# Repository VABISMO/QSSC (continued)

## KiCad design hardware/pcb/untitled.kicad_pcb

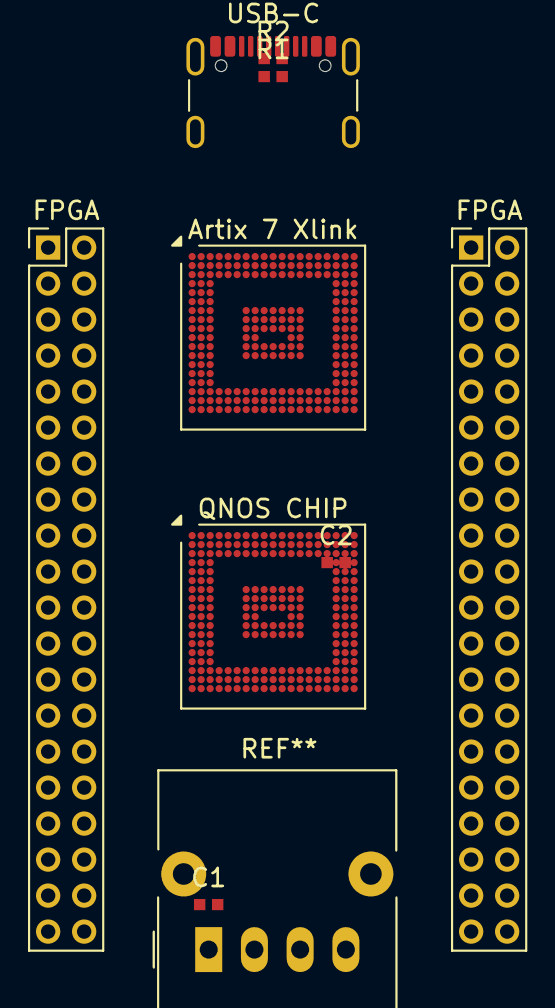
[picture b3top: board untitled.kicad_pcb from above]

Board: 2 copper layers, 9 parts (0 on the bottom side), 7 nets, no tracks yet.

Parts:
Artix 7 Xlink: Xilinx_CPG236
C1, C2: 0.1uF; C_0402_1005Metric
FPGA: PinHeader_2x20_P2.00mm_Vertical
FPGA#2: PinHeader_2x20_P2.00mm_Vertical
QNOS CHIP: QNOS CHIP; Xilinx_CPG236
R1, R2: 22; R_0402_1005Metric
USB-C: USB_C_Receptacle_GCT_USB4105-xx-A_16P_TopMnt_Hori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; USB_C_Receptacle_GCT_USB4105-xx-A_16P_TopMnt_Horizontal

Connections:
Fiber_Out: Artix 7 Xlink.D18, Artix 7 Xlink.U17, QNOS CHIP.D18, QNOS CHIP.U17
GND: Artix 7 Xlink.A1, Artix 7 Xlink.A3, Artix 7 Xlink.A5, Artix 7 Xlink.A7, Artix 7 Xlink.A9, Artix 7 Xlink.A19, Artix 7 Xlink.B3, Artix 7 Xlink.B5, Artix 7 Xlink.B7, Artix 7 Xlink.B8, Artix 7 Xlink.B9, Artix 7 Xlink.B14, Artix 7 Xlink.C2, Artix 7 Xlink.C3, Artix 7 Xlink.C4, Artix 7 Xlink.C6, Artix 7 Xlink.C10, Artix 7 Xlink.D3, Artix 7 Xlink.E3, Artix 7 Xlink.F1, Artix 7 Xlink.F2, Artix 7 Xlink.F19, Artix 7 Xlink.G1, Artix 7 Xlink.G8, Artix 7 Xlink.G11, Artix 7 Xlink.G19, Artix 7 Xlink.H7, Artix 7 Xlink.H8, Artix 7 Xlink.H11, Artix 7 Xlink.H12, Artix 7 Xlink.J11, Artix 7 Xlink.J12, Artix 7 Xlink.K12, Artix 7 Xlink.L8, Artix 7 Xlink.L11, Artix 7 Xlink.M9, Artix 7 Xlink.M11, Artix 7 Xlink.M13, Artix 7 Xlink.N9, Artix 7 Xlink.N12, Artix 7 Xlink.N13, Artix 7 Xlink.P2, Artix 7 Xlink.T19, Artix 7 Xlink.U6, Artix 7 Xlink.V1, Artix 7 Xlink.V6, Artix 7 Xlink.V18, Artix 7 Xlink.W1, Artix 7 Xlink.W12, Artix 7 Xlink.W17, C1.2, C2.2, QNOS CHIP.A1, QNOS CHIP.A3, QNOS CHIP.A5, QNOS CHIP.A7, QNOS CHIP.A9, QNOS CHIP.A19, QNOS CHIP.B3, QNOS CHIP.B5, QNOS CHIP.B7, QNOS CHIP.B9, QNOS CHIP.B14, QNOS CHIP.C2, QNOS CHIP.C3, QNOS CHIP.C4, QNOS CHIP.C6, QNOS CHIP.C10, QNOS CHIP.C19, QNOS CHIP.D3, QNOS CHIP.E3, QNOS CHIP.F1, QNOS CHIP.F2, QNOS CHIP.F19, QNOS CHIP.G1, QNOS CHIP.G8, QNOS CHIP.G11, QNOS CHIP.G19, QNOS CHIP.H7, QNOS CHIP.H8, QNOS CHIP.H11, QNOS CHIP.H12, QNOS CHIP.J11, QNOS CHIP.J12, QNOS CHIP.K12, QNOS CHIP.L8, QNOS CHIP.L11, QNOS CHIP.M9, QNOS CHIP.M11, QNOS CHIP.M13, QNOS CHIP.N9, QNOS CHIP.N12, QNOS CHIP.N13, QNOS CHIP.P2, QNOS CHIP.U6, QNOS CHIP.V1, QNOS CHIP.V6, QNOS CHIP.V18, QNOS CHIP.W1, QNOS CHIP.W12, QNOS CHIP.W17, USB-C.A1, USB-C.A5, USB-C.A12, USB-C.B1, USB-C.B5, USB-C.B12, USB-C.S1
USB_D+: Artix 7 Xlink.E19, R1.1, USB-C.A6, USB-C.B6
USB_D-: Artix 7 Xlink.E18, Artix 7 Xlink.F18, R2.1, USB-C.A7, USB-C.B7
Vcc: Artix 7 Xlink.C14, Artix 7 Xlink.C18, Artix 7 Xlink.F17, Artix 7 Xlink.M17, Artix 7 Xlink.R17, Artix 7 Xlink.U13, C1.1, C2.1, QNOS CHIP.F17, USB-C.A4, USB-C.A9, USB-C.B4, USB-C.B9
chip_D+: QNOS CHIP.E19, R1.2
chip_D-: QNOS CHIP.F18, R2.2

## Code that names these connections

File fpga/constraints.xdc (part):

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# Pin assignments are derived from the datasheet-correct CSG324 ball map
# (.tmpwork/fpga_csg324_map.json, parsed from the real KiCad Artix-7 symbol
# and verified against UG475 / DS181). All six VCCO banks are powered at
# 3.3 V (LVCMOS33). clk_100mhz is on a clock-capable (MRCC) pin.
#
# Parallel architecture: 64 emitters driven by 3x TLC5947 constant-current
# LED drivers over a 4-wire SPI (em_sclk/sin/xlat/blank), and 64 photo-
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# clk_100mhz -> B8, the P-side of an MRCC pair (IO_L..P.._MRCC_):
# per UG472 the single-ended clock INPUT takes the dedicated, delay-
# compensated route to the MMCM (no CLOCK_DEDICATED_ROUTE FALSE needed).
set_property PACKAGE_PIN B8   [get_ports clk_100mhz]
set_property IOSTANDARD LVCMOS33 [get_ports clk_100mhz]
create_clock -name sys_clk -period 10.000 [get_ports clk_100mhz]

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# (chip0 only -- push-pull, all 4 finish a simultaneous CONVST together),
# adc_cs[3:0] (per-chip select), adc_resetn (shared reset, active-low). The
# +/-5V range is HW-pin-strapped on each AD7616 (no MOSI / config writes).
set_property PACKAGE_PIN A18  [get_ports adc_convst]
set_property PACKAGE_PIN B18  [get_ports adc_sclk]
set_property PACKAGE_PIN D18  [get_ports adc_miso]
set_property PACKAGE_PIN E18  [get_ports adc_busy]
set_property PACKAGE_PIN M18  [get_ports adc_resetn]
set_property PACKAGE_PIN F18  [get_ports {adc_cs[0]}]
set_property PACKAGE_PIN G18  [get_ports {adc_cs[1]}]
set_property PACKAGE_PIN J18  [get_ports {adc_cs[2]}]
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# em_blank (global blank/PWM gate). 3x TLC5947 daisy-chain SIN->SOUT for 72
# channels (64 used); each emitter cathode is a TLC5947 OUTn, anode = +5V.
# 12-bit PWM grayscale per channel -> parallel multi-emitter drive.
set_property PACKAGE_PIN V1   [get_ports em_sclk]
set_property PACKAGE_PIN V2   [get_ports em_sin]
set_property PACKAGE_PIN V4   [get_ports em_xlat]
set_property PACKAGE_PIN V5   [get_ports em_blank]
set_property IOSTANDARD LVCMOS33 [get_ports em_sclk]
set_property IOSTANDARD LVCMOS33 [get_ports em_sin]
set_property IOSTANDARD LVCMOS33 [get_ports em_xlat]
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
# ---- MW RF-switch gate pulse (APPLY_PULSE duration) ------------------------
# Gates the external RF switch between the ADF4351 output and the antenna.
set_property PACKAGE_PIN L1   [get_ports mw_gate]
set_property IOSTANDARD LVCMOS33 [get_ports mw_gate]
set_property SLEW FAST [get_ports mw_gate]
set_property DRIVE 8   [get_ports mw_gate]
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# which gates the coil supply (high = a nonzero gradient is commanded).
# The DAC sets the gradient-coil current (I = Vdac/Rsense) for per-NV
# frequency addressing at 300 K; ODMR_SWEEP then counts resolved lines.
set_property PACKAGE_PIN V6   [get_ports grad_cs]
set_property PACKAGE_PIN V9   [get_ports grad_sclk]
set_property PACKAGE_PIN V12   [get_ports grad_mosi]
set_property PACKAGE_PIN V7   [get_ports grad_en]
set_property IOSTANDARD LVCMOS33 [get_ports grad_cs]
set_property IOSTANDARD LVCMOS33 [get_ports grad_sclk]
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
# ---- Timing: asynchronous inputs (audit #109) -------------------------------
# These off-chip inputs are fundamentally asynchronous to sys_clk and are
# 2-FF synchronised in the RTL (adc_busy in adc_reader.v, spi_pins[3]/MUXOUT
# in top_level.v). Without these false_path constraints Vivado times the
# input-pin -> first-flop path against sys_clk and reports benign
# setup/hold violations that mask REAL violations on the first P&R run.
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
